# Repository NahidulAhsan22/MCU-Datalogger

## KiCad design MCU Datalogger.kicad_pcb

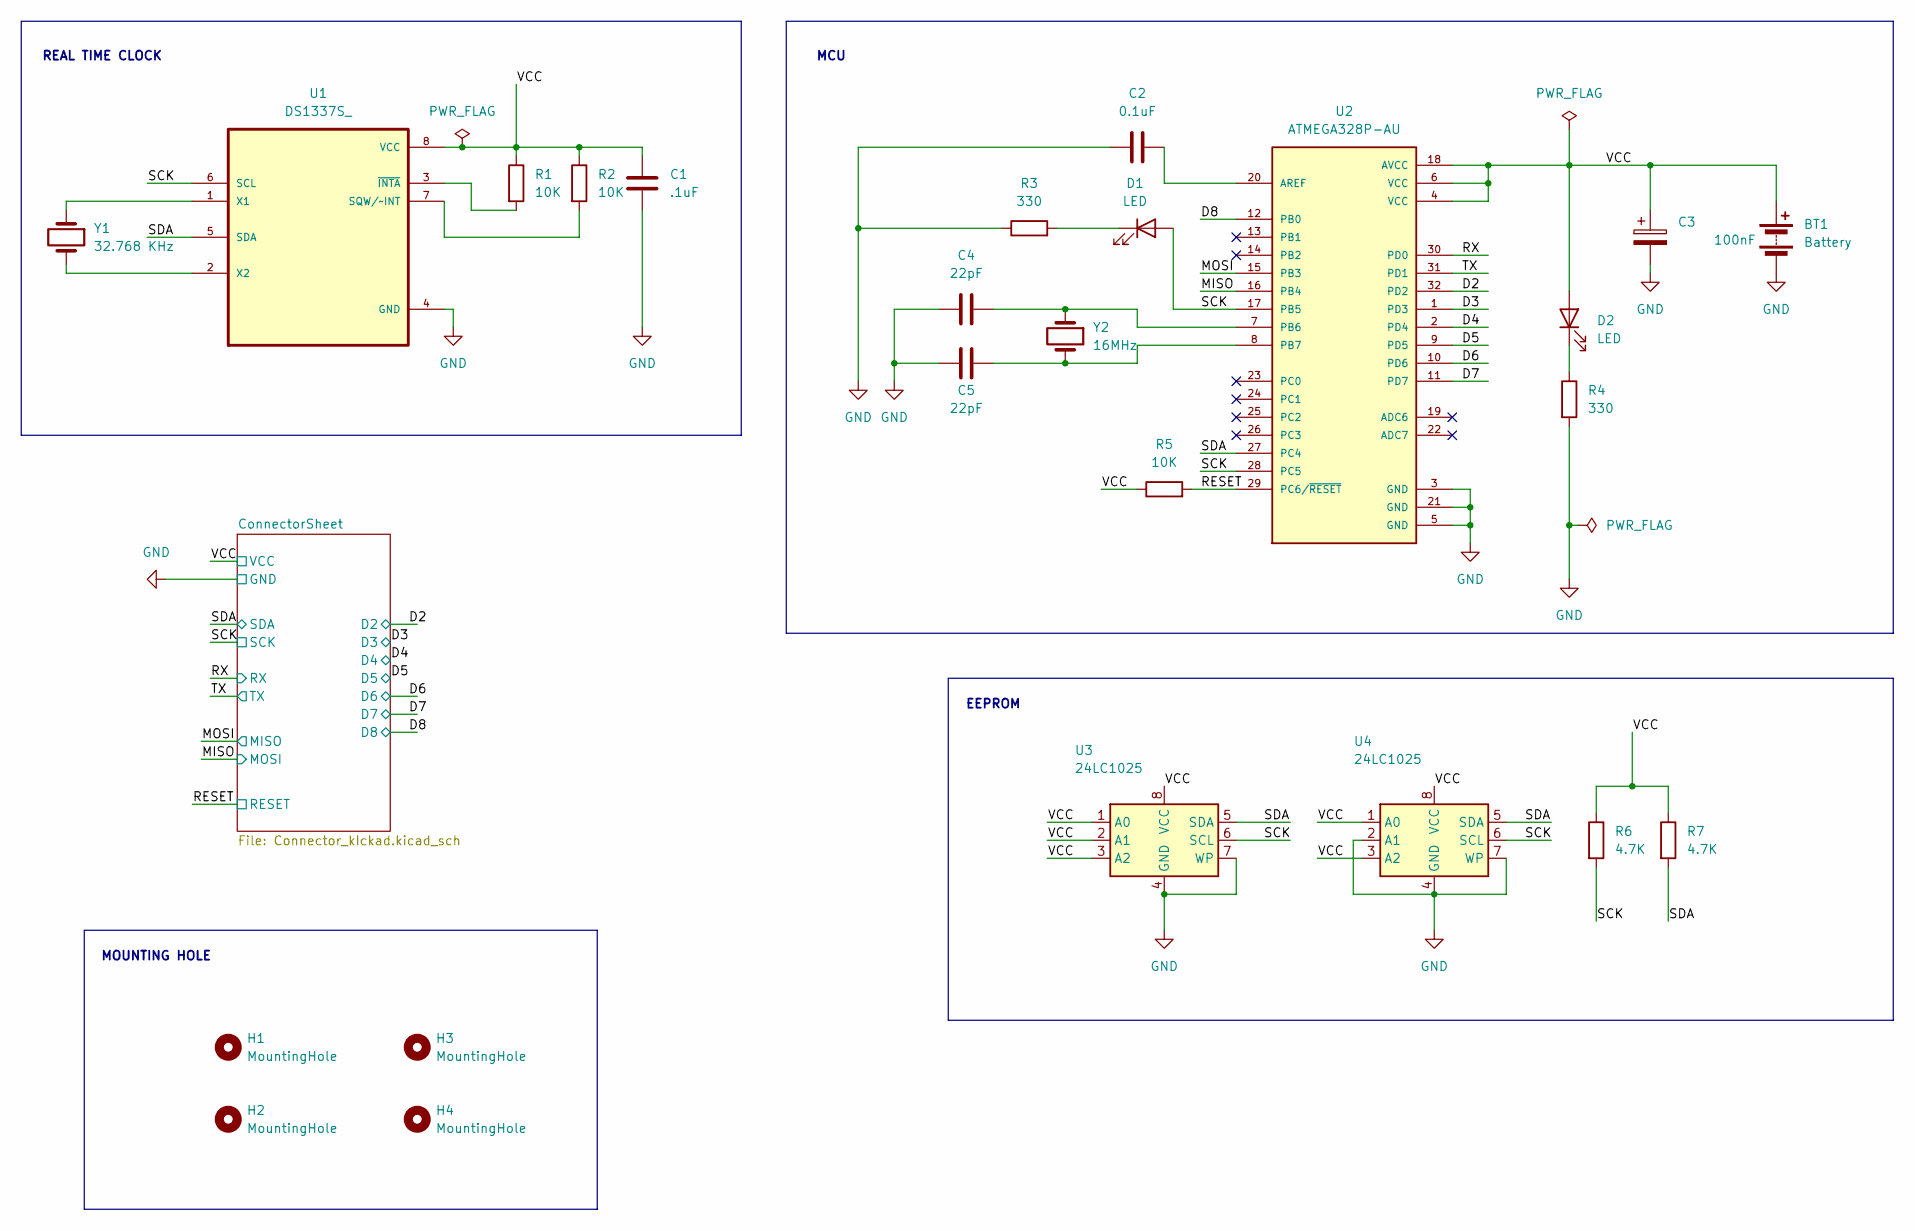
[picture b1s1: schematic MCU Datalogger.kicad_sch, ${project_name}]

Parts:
BT1: Battery; PinHeader_1x02_P2.54mm_Vertical
C1: .1uF; C_0805_2012Metric
C2: 0.1uF; C_0805_2012Metric
C3: 100nF; C_0805_2012Metric
C4, C5: 22pF; C_0805_2012Metric
D1, D2: LED; LED_0805_2012Metric
H1, H2, H3, H4: MountingHole; MountingHole_2.1mm
R1, R2, R5: 10K; R_0805_2012Metric
R3, R4: 330; R_0805_2012Metric
R6, R7: 4.7K; R_0805_2012Metric
U1: DS1337S_; SOIC127P600X175-8N
U2: ATMEGA328P-AU; QFP80P900X900X120-32N; PARTREV 8271A
U3, U4: 24LC1025; SOIC-8_5.23x5.23mm_P1.27mm
Y1: 32.768 KHz; Crystal_SMD_5032-2Pin_5.0x3.2mm_HandSoldering
Y2: 16MHz; Crystal_SMD_5032-2Pin_5.0x3.2mm_HandSoldering

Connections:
/D2: U2.32 (PD2); also elsewhere on the board
/D3: U2.1 (PD3); also elsewhere on the board
/D4: U2.2 (PD4); also elsewhere on the board
/D5: U2.9 (PD5); also elsewhere on the board
/D6: U2.10 (PD6); also elsewhere on the board
/D7: U2.11 (PD7); also elsewhere on the board
/D8: U2.12 (PB0); also elsewhere on the board
/MISO: U2.16 (PB4); also elsewhere on the board
/MOSI: U2.15 (PB3); also elsewhere on the board
/RESET: R5.2, U2.29 (PC6/~RESET); also elsewhere on the board
/RX: U2.30 (PD0); also elsewhere on the board
/SDA: R7.2, U1.5 (SDA), U2.27 (PC4), U3.5 (SDA), U4.5 (SDA); also elsewhere on the board
/VCC: BT1.1 (+), C1.1, C3.1, D2.2 (A), R1.1, R2.1, R5.1, R6.1, R7.1, U1.8 (VCC), U2.4 (VCC), U2.6 (VCC), U2.18 (AVCC), U3.1 (A0), U3.2 (A1), U3.3 (A2), U3.8 (VCC), U4.1 (A0), U4.3 (A2), U4.8 (VCC); also elsewhere on the board
GND: BT1.2 (-), C1.2, C2.1, C3.2, C4.2, C5.2, R3.1, R4.2, U1.4 (GND), U2.3 (GND), U2.5 (GND), U2.21 (GND), U3.4 (GND), U3.7 (WP), U4.2 (A1), U4.4 (GND), U4.7 (WP); also elsewhere on the board
unnamed: D1.1 (K), R3.2
unnamed: D2.1 (K), R4.1
unnamed: R2.2, U1.7 (SQW/~INT)
unnamed: U1.1 (X1), Y1.1
unnamed: U1.2 (X2), Y1.2
unnamed: R1.2, U1.3 (~INTA)
unnamed: C2.2, U2.20 (AREF)
unnamed: C4.1, U2.7 (PB6), Y2.1
unnamed: C5.1, U2.8 (PB7), Y2.2

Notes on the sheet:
MOUNTING HOLE
EEPROM
REAL TIME CLOCK
MCU

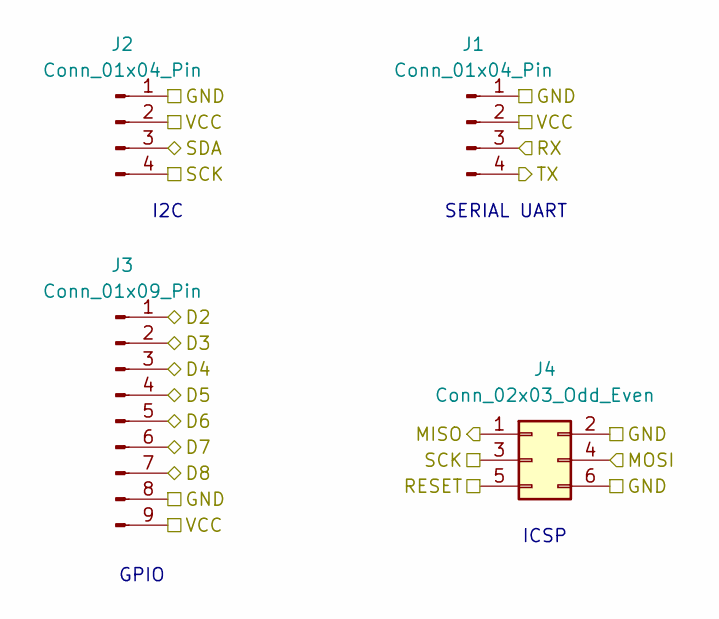
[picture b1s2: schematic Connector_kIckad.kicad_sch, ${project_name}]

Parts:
J1, J2: Conn_01x04_Pin; PinHeader_1x04_P2.54mm_Vertical
J3: Conn_01x09_Pin; PinHeader_1x09_P2.54mm_Vertical
J4: Conn_02x03_Odd_Even; PinHeader_2x03_P2.54mm_Vertical

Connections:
/D2: J3.1; also elsewhere on the board
/D3: J3.2; also elsewhere on the board
/D4: J3.3; also elsewhere on the board
/D5: J3.4; also elsewhere on the board
/D6: J3.5; also elsewhere on the board
/D7: J3.6; also elsewhere on the board
/D8: J3.7; also elsewhere on the board
/MISO: J4.4; also elsewhere on the board
/MOSI: J4.1; also elsewhere on the board
/RESET: J4.5; also elsewhere on the board
/RX: J2.3; also elsewhere on the board
/SDA: J1.3; also elsewhere on the board
/VCC: J1.2, J2.2, J3.9; also elsewhere on the board
GND: J1.1, J2.1, J3.8, J4.2, J4.6; also elsewhere on the board

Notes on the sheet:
SERIAL UART
I2C
ICSP
GPIO

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
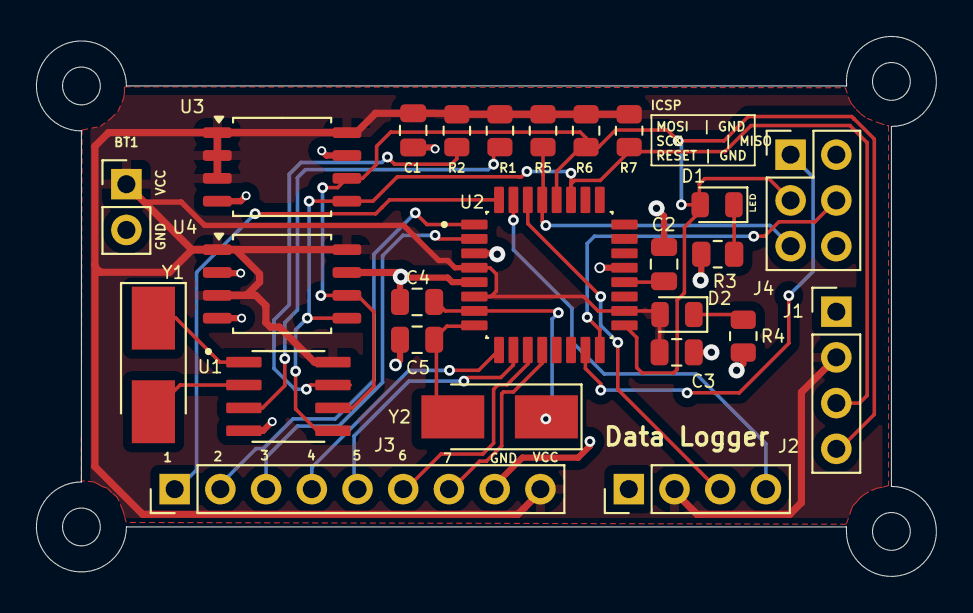
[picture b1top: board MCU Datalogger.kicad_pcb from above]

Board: 2 copper layers, 50.0 x 30.0 mm, 29 parts (0 on the bottom side), 25 nets.

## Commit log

2024-09-24 test
2024-09-24 added connection
2024-09-26 Connector level adding
2024-09-26 Connector adding
2024-09-26 Changes both sheet
2024-09-26 After comment
2024-09-26 Initail Layout
2024-09-28 Initial Routing
2024-09-30 Layout complete
2024-09-30 SKILLSCREEN UPDATE
2024-09-30 GARBER FILE
2024-11-14 4 layer Initail
2024-12-04 4 layer without violation
2024-12-04 4 layer garber files
